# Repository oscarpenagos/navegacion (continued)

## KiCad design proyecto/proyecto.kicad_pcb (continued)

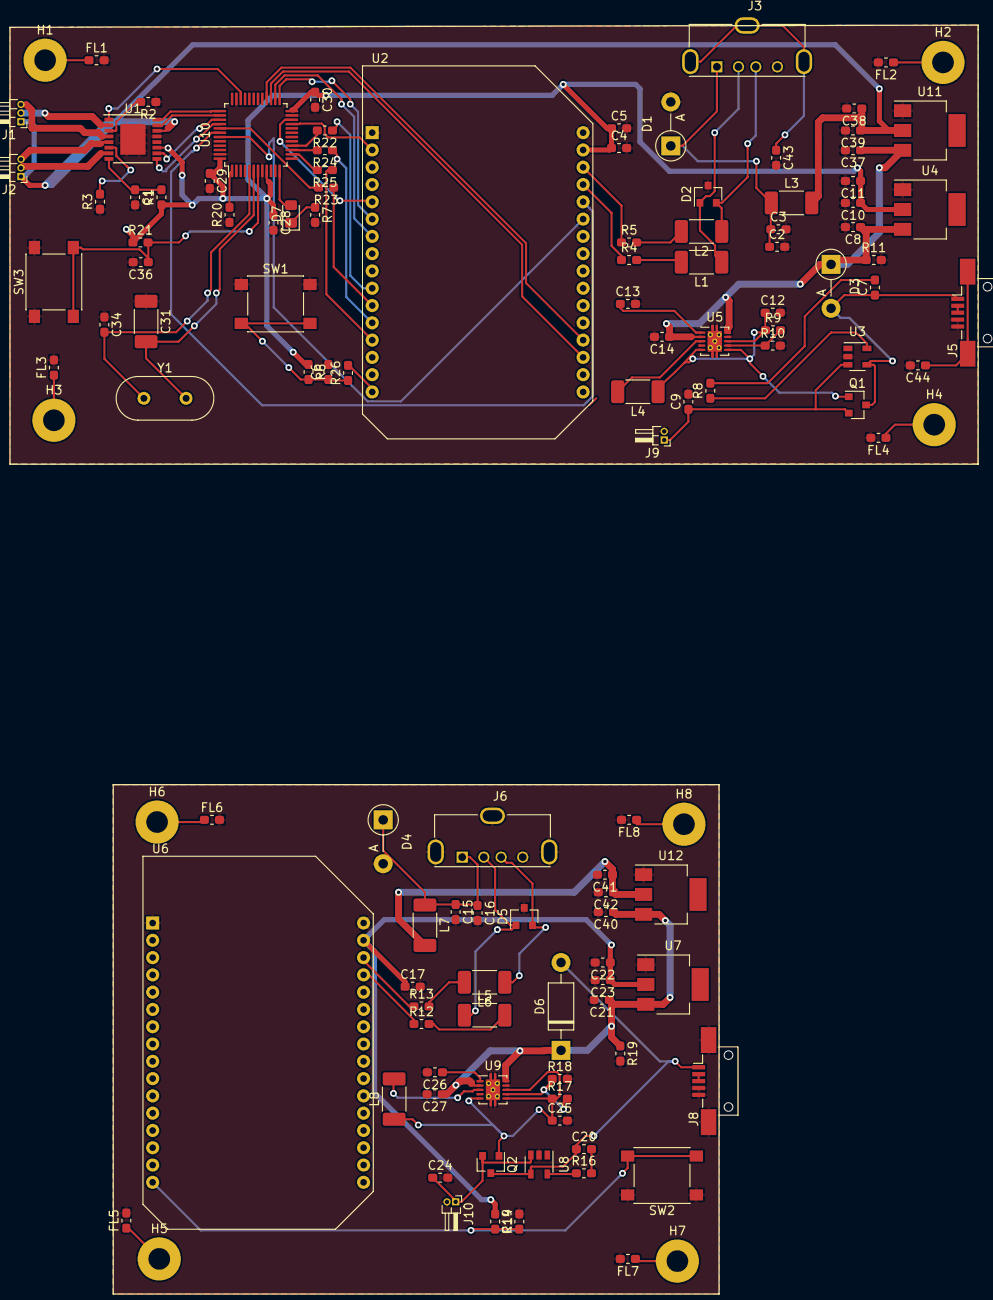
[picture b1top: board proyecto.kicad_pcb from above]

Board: 2 copper layers, 122 parts (0 on the bottom side), 87 nets.

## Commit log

2020-04-14 Create kicad
2020-06-16 Create proyecto1
